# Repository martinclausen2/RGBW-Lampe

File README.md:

# RGBW-Lampe

The "RGBW-Lampe" projects allows to create full color lighting appliances.

## Features

- Four independent LED driver channels
  - Optimal to drive RGBW LED modules.
  - Mood light mode
  - High dynamic dimming range ideal for color mixing
- Status LED to indicate power on, channel, standby, and network status
- Brightness measurement to adjust brightness at power on
- IR remote control (receiver and sender)
  -	Option to network devices
- Single rotational encoder and switch needed to control
- Embedded terminal to control settings, clock, and alarms available via WLAN
  - Connect to home automation via MQTT
  - Adjust settings via exposed terminal
- Protected electronic power switch

## Technical Features
- ARM Cortex M3 based STM32L151A microcontroller
  - EEPROM for permanent storage of settings
- ESP8266 based WLAN connectivity ESP-12
- RC5 based communication (sender and receiver)
- Four PT4115 step-down LED driver
  - PWM input
  - LED driving current up to 1A
  - Short rise time of driving current to drive LED with very low duty PWM signals needed for color mixing
- Input voltage 9 to 15 V
- High dynamic brightness measurement with low cost phototransistor SFH320
- Pin header for observing and intercepting serial communication between MCU and WLAN module
  - Debugging
  - Initial programming of WLAN module
  - Redirecting communication to / from serial port of J-LINK
- PCB prepared (not used in current software) for 
  - Acceleration sensor
  - Pin headers for extension with additional I2C devices, LCD, or LED drivers
  - EEPROM from 24CXXX series with I2C connection - currently the MCU's internal EEPROM is utilized, the EEPROM can be populated if other STM32 MCU are to be used which do not contain a EEPROM

# Design description

## Hardware

### WLAN
The low cost WLAN module ESP-12 based on the ESP8266 is used to connect to home automation, expose an interface to configure the appliance, and to obtain date and time via NTP.

### MCU
The STM32L1 series features for this application relevant features like a large number of timers, and an embedded EEPROM.

The MCU can be programmed and debugged via SWD accessible through a custom pin header, that also exposes the serial port.

### LED Driver
Color mixing requires a large dimming range, which was realized via PWM dimming. The LED driver PT4115 has a short rise time allowing to create also very short current pulses to drive the LEDs at low levels.

### Logic Power Supply
A step down voltage regulator generates 3.3 V logic supply. It needs to be capable to provide good load regulation and sufficient current for the WLAN module as well as the IR-LED.

### RC5 receiver and sender

A IR emitting diode is driven by a small MOSFET from the PWM output of a timer in the MCU to send RC5 commands.

To receive RC5 commands the output of the IR receiver is sampled at a rate of about 4.5kHz by the MCU. The power supply of the IR receiver is cut in standby mode to prevent the battery to be drained prematurely.

### Brightness Sensor

The ambient brightness is sensed via an inexpensive and broadly available phototransistor SFA 320. To enhance the dynamic range, the MCU can switch the bias current between two different levels.
The precision is fully sufficient to adjust the brightness of the power LEDs at power on and dim the status LED in standby.

## Software

### WLAN Module

The time is fetched on start and about once per day later from the NTP server.

The terminal is exposed via port 22.

## Known Limitations
- The WLAN module may lose its connection when allowing Protected Management Frames (PMF) by the WLAN access point.
  - For Fritz!Box the option is found under WLAN -> Security -> Additional Security Settings
	 - German: Leave the option "Unterstützung für geschützte Anmeldungen von WLAN-Geräten (PMF) aktivieren" **unchecked**
- The WLAN module has fixed settings. Recompilation and flashing of the ESP8266 is needed to change them.
  - MQTT (device?.h)
  - WLAN (credentials.h)
  - NTP server (device?.h)
- The WLAN module exposes the ports of terminal (22) and MQTT without any protection.
- Commands received via MQTT and updates from the NTP server are injected into the terminal communication. Commands from the terminal might be interrupted by MQTT or time updates.
- OTA updates of the STM32 are not implemented yet.
- During power on, the LED driver operate at full current for a fraction of a second.

# User Manual

The user interface is rather simplistic.

Turning the encoder increases or decreases the brightness.
The integrated push button is used to select functionality and change between on and off.
Detailed settings can be adjusted via the serial terminal.

Coming from standby a short button press switches the light on. A long button press activates the networked mode, where other compatible lighting appliances receive commands to follow on, off, and brightness settings.

When the appliance in on the short button press selects between the four individual LED strings and a mode where the brightness is modulated between the channels.

When the button is pressed, the status led previews a for a short time the next selected functionality.

Standby can be reached via a long button pressed from power on mode.

| LED Color 	| Condition | Status   | 
| :------------ | :------ | :------- |
| red			|         | standby  |
| white			|         | power on |
| blue flashing | 1 flash, pause | WLAN module booting |
| blue flashing | 3 flash, pause | No time from NTP server obtained |
| green flash	| while adjusting brightness | maximum brightness reached |
| red flash		| while adjusting brightness | minimum brightness reached |
| white flash	| pressing the button short | selected white LED channel  |
| red flash		| pressing the button short | selected red LED channel |
| blue flash	| pressing the button short | selected blue LED channel |
| green flash	| pressing the button short | selected green LED channel |
| pink flash	| pressing the button short | selected mood light mode |
| green flash	| pressing the button very long | cancel button pressed |

The white flash is actually not visible, since the LED is already shining white.

# Configuration Manual

The serial port uses the following parameter 115200 Baud rate, data site 8, parity none, stop bits 1.

This terminal is exposed via the WLAN module to the user on port 22.

The commands can be listed by sending the command `help`.

## WLAN

WLAN credentials must be set at compile time in the file `credentials.h`.

## MQTT

Broker and node name must be defined at compile time in the file `device?.h`:

	#define MQTTbroker "192.168.178.123"
	#define nodename "RGBW-Lampe1"

Topics might be freely defined at compile time in the file `device?.h`. The following section contains some examples.

The appliance publishes to different topics its status:

	#define publishtopicstatus "RGBW-Lampe/1/status"
	#define publishtopicNTP "RGBW-Lampe/1/NTP"
	#define publishtopicswitch "RGBW-Lampe/1/switch"

The appliance subscribes to two topics defined at compile time in the file `device?.h`. The names are here choosen to be independent of the device id.

### MQTT to terminal forwarder

	#define subscribetopic "RGBW-Lampe"
All data is forwarded to the terminal of the MCU. See terminal section below for details.

### Switch

	#define subscribetopicswitch "RGBW-Lampe/switch"
The commands are `on` and `off`

## Commands Terminal

The terminal is accessible at three different routes:

- Interception of the serial WLAN - MCU communication through the pin header on the PCB
- Port 22 of the WLAN module
- MQTT topic defined by `subscribetopic`

### Set Brightness

	bright [type] <-c channel_no> <-b brightness_value>

set brightness values

| Type | Description |
| :--- | :--------- |
| 0 | Brightness last used before lights were switched off. |
| 1 | Minimum brightness when switched on |
| 2 | Maximum brightness any time |
| 3 | Maximum brightness when an alarm is triggered |
| 4 | PWM offset for brightness |
| 5 | Current brightness |

### Get External Brightness

	getextbright

Get the external brightness from the phototransistor

### Infrared Remote Control

	remote <-a address> <-rm receiver mode> <-sm sender mode> <-sa send address> <-sd send data>

set infrared remote parameters

| Mode | Decription |
| :--- | :--------- |
| 0 | Off |
| 1 | Alarm |
| 2 | Condional |
| 3 | All |

### Set Date and Time

	time [hour] [minute] [second]

set time of RTC

	date [2 digit year] [month] [day] [w] with w weekday

set date of RTC

	timestamp

get date and time from RTC

### Alarm

	alarmschedule [alarm no] <-w weekday> <-h hour> <-m minute>

set alarm schedule

	alarmsetting <-f time to fade-in light> <-si time to signal> <-sn snooze time>

set alarm parameters
	
	alarm <-a 1 | 0> <-s alarm skip count>

trigger, reset, set alarm skip count

### Beep

	beep <-s 1 | 0> volume - <-v volume> volume level - <-vl 1 | 0>

Call without any parameters to hear a beep. Using the `-s` parameter allows to turn the acoustic signal on and off. Volume allows for a continues selection of the volume between 0 and 255. The volume level sets the range in which the volume is adjustable.

### Power

	power <-l 1 | 0>

switch light.

### Reset Settings

	reset

reset settings to factory defaults

### Status LED

	statusled [flash count]

flash status led

### Mood light

	fadelight <-f 1 | 0> time - <-t time> <-b brightness> <-mb maximum brightness>

switch and parameterize on mood light

### DebugCmd

	debug

Dummy command to absorb debug messages from host.

### Reset WLAN Module

	resetesp

Reset network controller ESP8266.

### Version

	version

show STM32 software version

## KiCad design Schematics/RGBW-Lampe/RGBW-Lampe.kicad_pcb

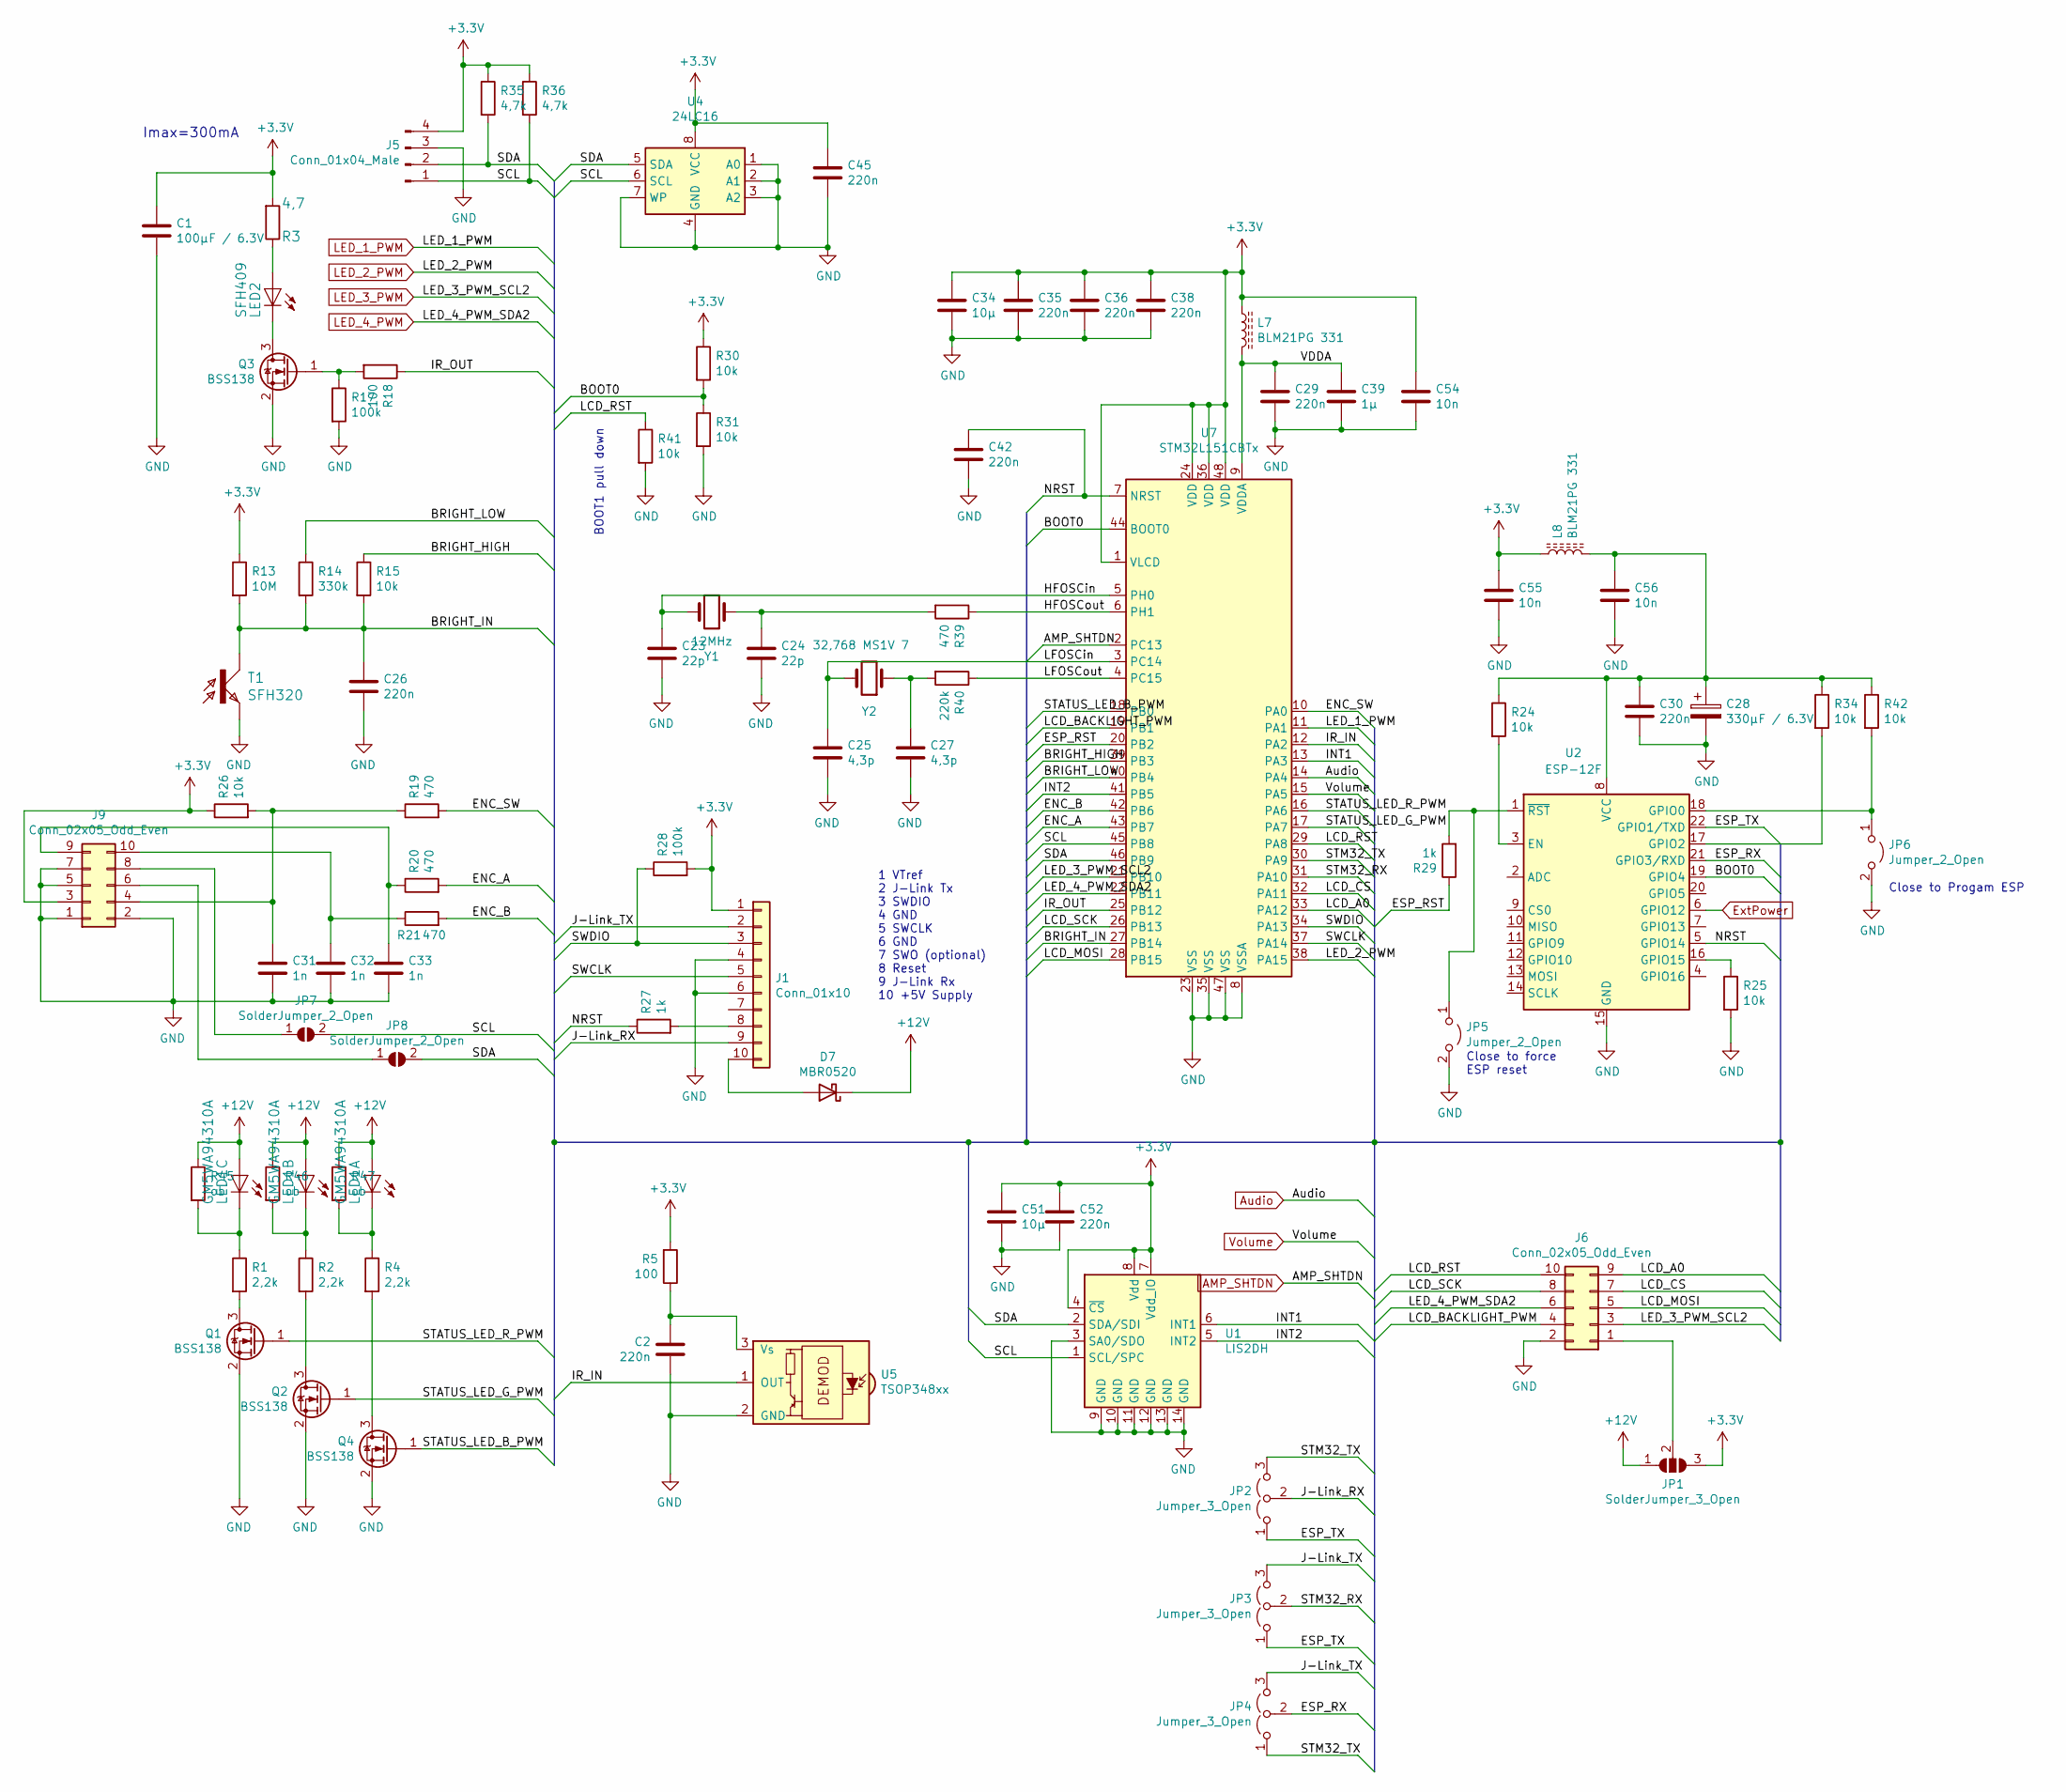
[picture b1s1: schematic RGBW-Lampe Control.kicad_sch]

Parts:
C1: 100µF / 6.3V; C_1210_3225Metric
C2, C26, C29, C30, C35, C36, C38, C42, C45, C52: 220n; C_0603_1608Metric
C23, C24: 22p; C_0603_1608Metric
C25, C27: 4,3p; C_0603_1608Metric
C28: 330µF / 6.3V; CP_Radial_D6.3mm_P2.50mm
C31, C32, C33: 1n; C_0603_1608Metric
C34, C51: 10µ; C_0805_2012Metric
C39: 1µ; C_0805_2012Metric
C54, C55, C56: 10n; C_0603_1608Metric
D7: MBR0520; D_SOD-123
J1: Conn_01x10; PinSocket_1x10_P1.27mm_Vertical
J5: Conn_01x04_Male; PinHeader_1x04_P2.54mm_Vertical
J6, J9: Conn_02x05_Odd_Even; IDC-Header_2x05_P2.54mm_Vertical
JP1: SolderJumper_3_Open; SolderJumper-3_P1.3mm_Open_RoundedPad1.0x1.5mm_NumberLabels
JP2, JP3, JP4: Jumper_3_Open; PinHeader_1x03_P2.54mm_Vertical
JP5, JP6: Jumper_2_Open; PinHeader_1x02_P2.54mm_Vertical
JP7, JP8: SolderJumper_2_Open; SolderJumper-2_P1.3mm_Open_Pad1.0x1.5mm
L7, L8: BLM21PG 331; L_0805_2012Metric
LED1: GM5WA94310A
LED2: SFH409; LED3MM
Q1, Q2, Q3, Q4: BSS138; SOT-23
R1, R2, R4: 2,2k; R_0805_2012Metric
R3: 4,7; R_1206_3216Metric
R5, R18: 100; R_0805_2012Metric
R13: 10M; R_0805_2012Metric
R14: 330k; R_0805_2012Metric
R15, R24, R25, R26, R30, R31, R34, R41, R42: 10k; R_0805_2012Metric
R17, R28: 100k; R_0805_2012Metric
R19, R20, R21, R39: 470; R_0805_2012Metric
R27, R29: 1k; R_0805_2012Metric
R35, R36: 4,7k; R_0805_2012Metric
R40: 220k; R_0805_2012Metric
R45, R46, R47: ob; R_0805_2012Metric
T1: SFH320; LED_PLCC-2
U1: LIS2DH; LGA-14_2x2mm_P0.35mm_LayoutBorder3x4y
U2: ESP-12F; ESP-12E
U4: 24LC16; SOIC-8_3.9x4.9mm_P1.27mm
U5: TSOP348xx; Vishay_MOLD-3Pin
U7: STM32L151CBTx; LQFP-48_7x7mm_P0.5mm
Y1: 12MHz; Crystal_SMD_EuroQuartz_MT-4Pin_3.2x2.5mm
Y2: 32,768 MS1V 7; Crystal_SMD_MicroCrystal_MS1V-T1K

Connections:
+3V3: C1.1, C34.1, C35.1, C36.1, C38.1, C45.1, C51.1, C52.1, C54.1, C55.1, J1.1, J5.4, J9.3, JP1.3 (B), L7.1, L8.1, R3.2, R5.2, R13.1, R26.1, R28.2, R30.1, R35.1, R36.1, U1.4 (~CS), U1.7 (Vdd_IO), U1.8 (Vdd), U4.8 (VCC), U7.1 (VLCD), U7.24 (VDD), U7.36 (VDD), U7.48 (VDD); also elsewhere on the board
+12V: D7.1 (K), JP1.1 (A), LED1.1 (A), LED1.2 (A), LED1.3 (A), R45.1, R46.1, R47.1; also elsewhere on the board
/Control/BOOT0: R30.2, R31.1, U2.19 (GPIO4), U7.44 (BOOT0)
/Control/BRIGHT_HIGH: R15.1, U7.39 (PB3)
/Control/BRIGHT_IN: C26.1, R13.2, R14.2, R15.2, T1.1 (C), U7.27 (PB14)
/Control/BRIGHT_LOW: R14.1, U7.40 (PB4)
/Control/ENC_A: R20.2, U7.43 (PB7)
/Control/ENC_B: R21.2, U7.42 (PB6)
/Control/ENC_SW: R19.2, U7.10 (PA0)
/Control/ESP_RST: R29.1, U7.20 (PB2)
/Control/ESP_RX: JP4.2 (C), U2.21 (GPIO3/RXD)
/Control/ESP_TX: JP2.1 (A), JP3.1 (A), U2.22 (GPIO1/TXD)
/Control/HFOSCin: C23.1, U7.5 (PH0), Y1.2
/Control/HFOSCout: R39.1, U7.6 (PH1)
/Control/INT1: U1.6 (INT1), U7.13 (PA3)
/Control/INT2: U1.5 (INT2), U7.41 (PB5)
/Control/IR_IN: U5.1 (OUT), U7.12 (PA2)
/Control/IR_OUT: R18.1, U7.25 (PB12)
/Control/J-Link_RX: J1.9, JP2.2 (C)
/Control/J-Link_TX: J1.2, JP3.3 (B), JP4.3 (B)
/Control/LCD_A0: J6.9, U7.33 (PA12)
/Control/LCD_BACKLIGHT_PWM: J6.4, U7.19 (PB1)
/Control/LCD_CS: J6.7, U7.32 (PA11)
/Control/LCD_MOSI: J6.5, U7.28 (PB15)
/Control/LCD_RST: J6.10, R41.1, U7.29 (PA8)
/Control/LCD_SCK: J6.8, U7.26 (PB13)
/Control/LFOSCin: C25.1, U7.3 (PC14), Y2.2
/Control/LFOSCout: R40.1, U7.4 (PC15)
/Control/NRST: C42.1, R27.1, U2.5 (GPIO14), U7.7 (NRST)
/Control/SCL: J5.1, JP7.2 (B), R36.2, U1.1 (SCL/SPC), U4.6 (SCL), U7.45 (PB8)
/Control/SDA: J5.2, JP8.2 (B), R35.2, U1.2 (SDA/SDI), U4.5 (SDA), U7.46 (PB9)
/Control/STATUS_LED_B_PWM: Q4.1 (G), U7.18 (PB0)
/Control/STATUS_LED_G_PWM: Q2.1 (G), U7.17 (PA7)
/Control/STATUS_LED_R_PWM: Q1.1 (G), U7.16 (PA6)
/Control/STM32_RX: JP3.2 (C), U7.31 (PA10)
/Control/STM32_TX: JP2.3 (B), JP4.1 (A), U7.30 (PA9)
/Control/SWCLK: J1.5, U7.37 (PA14)
/Control/SWDIO: J1.3, R28.1, U7.34 (PA13)
/Control/VDDA: C29.1, C39.1, L7.2, U7.9 (VDDA)
AMP_SHTDN: U7.2 (PC13); also elsewhere on the board
Audio: U7.14 (PA4); also elsewhere on the board
ExtPower: U2.6 (GPIO12); also elsewhere on the board
GND: C1.2, C2.2, C23.2, C24.2, C25.2, C26.2, C27.2, C28.2, C29.2, C30.2, C31.2, C32.2, C33.2, C34.2, C35.2, C36.2, C38.2, C39.2, C42.2, C45.2, C51.2, C52.2, C54.2, C55.2, C56.2, J1.4, J1.6, J5.3, J6.2, J9.1, J9.2, J9.5, J9.7, JP5.2 (B), JP6.2 (B), Q1.2 (S), Q2.2 (S), Q3.2 (S), Q4.2 (S), R17.2, R25.2, R31.2, R41.2, T1.2 (E), U1.3 (SA0/SDO), U1.9 (GND), U1.10 (GND), U1.11 (GND), U1.12 (GND), U1.13 (GND), U1.14 (GND), U2.15 (GND), U4.1 (A0), U4.2 (A1), U4.3 (A2), U4.4 (GND), U4.7 (WP), U5.2 (GND), U7.8 (VSSA), U7.23 (VSS), U7.35 (VSS), U7.47 (VSS); also elsewhere on the board
LED_1_PWM: U7.11 (PA1); also elsewhere on the board
LED_2_PWM: U7.38 (PA15); also elsewhere on the board
LED_3_PWM: J6.3, U7.21 (PB10); also elsewhere on the board
LED_4_PWM: J6.6, U7.22 (PB11); also elsewhere on the board
unnamed: C2.1, R5.1, U5.3 (Vs)
unnamed: C24.1, R39.2, Y1.1
unnamed: C27.1, R40.2, Y2.1
unnamed: C28.1, C30.1, C56.1, L8.2, R24.1, R34.1, R42.1, U2.8 (VCC)
unnamed: C31.1, J9.4, R19.1, R26.2
unnamed: C32.1, J9.10, R21.1
unnamed: C33.1, J9.9, R20.1
unnamed: D7.2 (A), J1.10
unnamed: J1.8, R27.2
unnamed: J6.1, JP1.2 (C)
unnamed: J9.6, JP8.1 (A)
unnamed: J9.8, JP7.1 (A)
unnamed: JP5.1 (A), R29.2, U2.1 (~RST)
unnamed: JP6.1 (A), R42.2, U2.18 (GPIO0)
unnamed: LED1.4 (C), R2.1, R46.2
unnamed: LED1.5 (C), R4.1, R47.2
unnamed: LED1.6 (C), R1.1, R45.2
unnamed: LED2.A, R3.1
unnamed: LED2.K (C), Q3.3 (D)
unnamed: Q1.3 (D), R1.2
unnamed: Q2.3 (D), R2.2
unnamed: Q3.1 (G), R17.1, R18.2
unnamed: Q4.3 (D), R4.2
unnamed: R24.2, U2.3 (EN)
unnamed: R25.1, U2.16 (GPIO15)
unnamed: R34.2, U2.17 (GPIO2)
Volume: U7.15 (PA5); also elsewhere on the board

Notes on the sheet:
BOOT1 pull down
1 VTref 2 J-Link Tx 3 SWDIO 4 GND 5 SWCLK 6 GND 7 SWO (optional) 8 Reset 9 J-Link Rx 10 +5V Supply
Close to Progam ESP
Imax=300mA
Close to force ESP reset

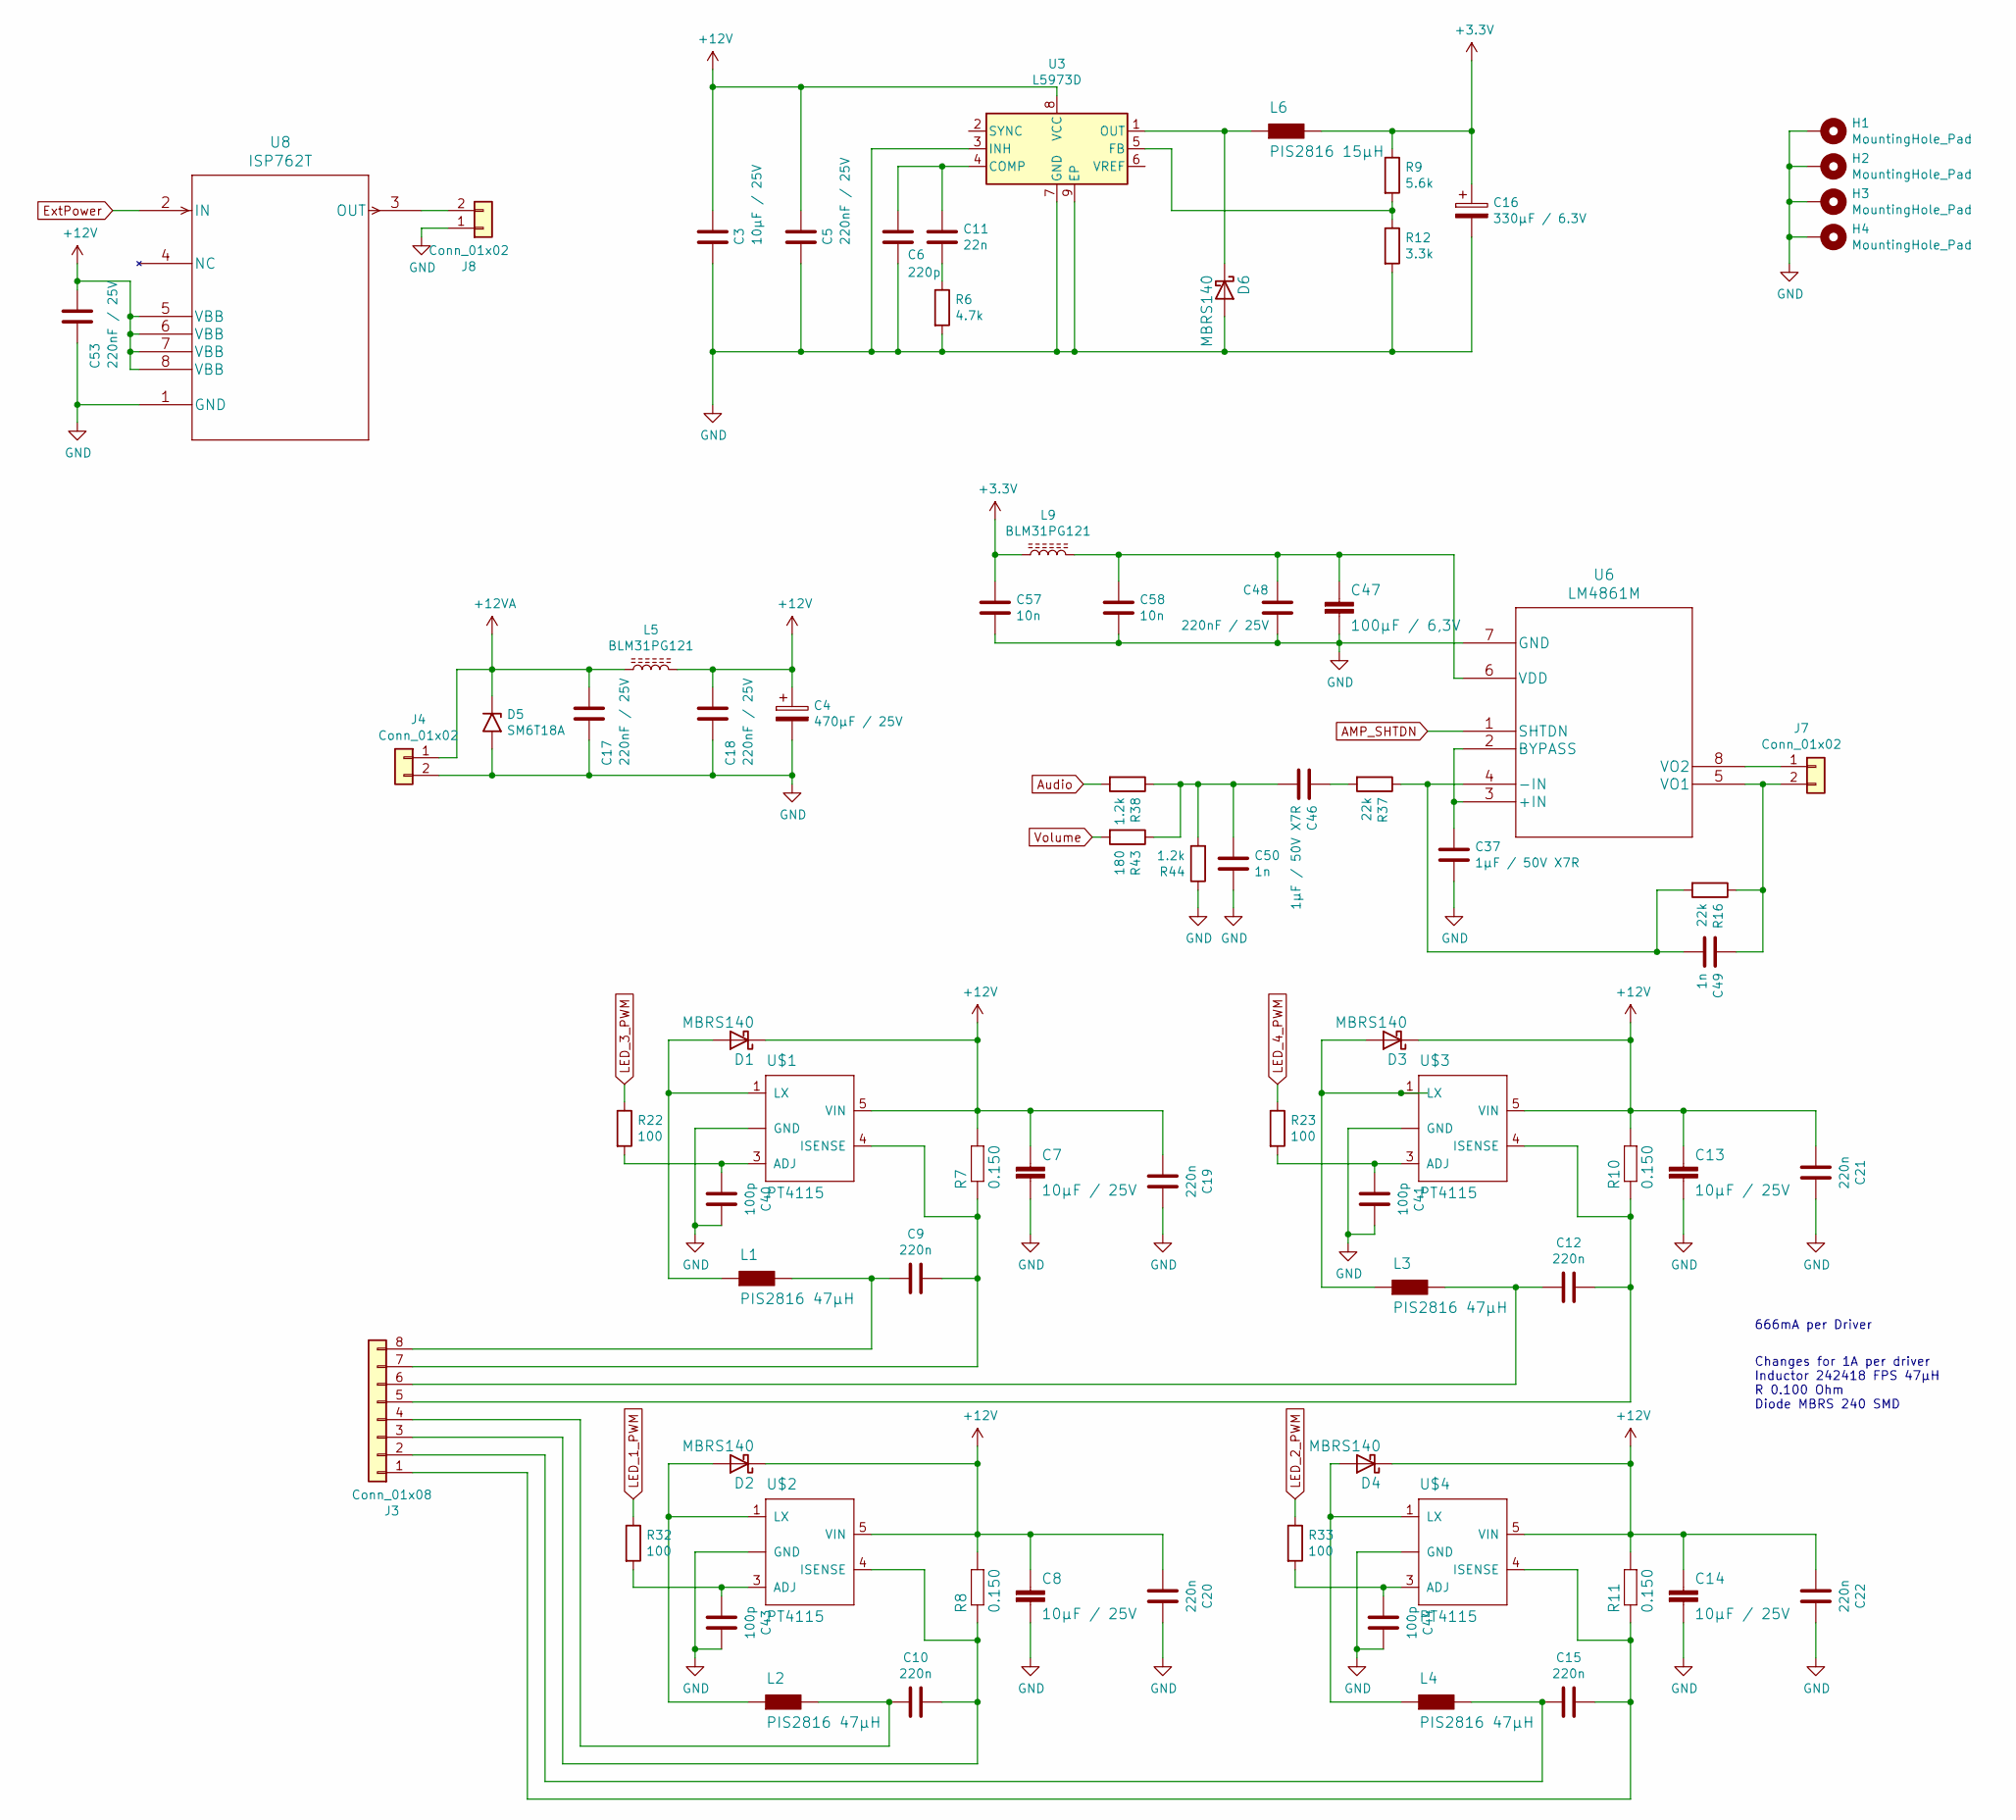
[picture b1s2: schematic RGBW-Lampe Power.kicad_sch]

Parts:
C3, C7, C8, C13, C14: 10µF / 25V; C_1206_3216Metric
C4: 470µF / 25V; CP_Radial_D8.0mm_P3.50mm
C5, C17, C18, C48, C53: 220nF / 25V; C_0603_1608Metric
C6: 220p; C_0603_1608Metric
C9, C10, C12, C15, C19, C20, C21, C22: 220n; C_0603_1608Metric
C11: 22n; C_0603_1608Metric
C16: 330µF / 6.3V; CP_Radial_D6.3mm_P2.50mm
C37, C46: 1µF / 50V X7R; C_1206_3216Metric
C40, C41, C43, C44: 100p; C_0603_1608Metric
C47: 100µF / 6,3V; C_1206_3216Metric
C49, C50: 1n; C_0603_1608Metric
C57, C58: 10n; C_0603_1608Metric
D1, D2, D3, D4, D6: MBRS140; D_SMB
D5: SM6T18A; D_SMB
H1, H2, H3, H4: MountingHole_Pad; MountingHole_3.2mm_M3_DIN965_Pad
J3: Conn_01x08; JST_XH_B8B-XH-A_1x08_P2.50mm_Vertical
J4, J7, J8: Conn_01x02; JST_XH_B2B-XH-A_1x02_P2.50mm_Vertical
L1, L2, L3, L4: PIS2816 47µH; PIS2816
L5, L9: BLM31PG121; L_1206_3216Metric
L6: PIS2816 15µH; PIS2816
R6: 4.7k; R_0805_2012Metric
R7, R8, R10, R11: 0.150; R_1210_3225Metric
R9: 5.6k; R_0805_2012Metric
R12: 3.3k; R_0805_2012Metric
R16, R37: 22k; R_0805_2012Metric
R22, R23, R32, R33: 100; R_0805_2012Metric
R38, R44: 1.2k; R_0805_2012Metric
R43: 180; R_0805_2012Metric
U3: L5973D; HSOP-8-1EP_3.9x4.9mm_P1.27mm_EP2.41x3.1mm_ThermalVias
U6: LM4861M
U8: ISP762T
U$1, U$2, U$3, U$4: PT4115; SOT89-5

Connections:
+3V3: C16.1, C57.2, L6.P$2, L9.1, R9.1; also elsewhere on the board
+12V: C3.1, C4.1, C5.2, C7.1, C8.1, C13.1, C14.1, C18.2, C19.2, C20.2, C21.2, C22.2, C53.2, D1.1 (K), D2.1 (K), D3.1 (K), D4.1 (K), L5.2, R7.2, R8.2, R10.2, R11.2, U3.8 (VCC), U8.5 (VBB), U8.6 (VBB), U8.7 (VBB), U8.8 (VBB), U$1.5 (VIN), U$2.5 (VIN), U$3.5 (VIN), U$4.5 (VIN); also elsewhere on the board
+12VA: C17.2, D5.1 (A1), J4.1, L5.1
AMP_SHTDN: U6.1 (SHTDN); also elsewhere on the board
Audio: R38.2; also elsewhere on the board
ExtPower: U8.2 (IN); also elsewhere on the board
GND: C3.2, C4.2, C5.1, C6.2, C7.2, C8.2, C13.2, C14.2, C16.2, C17.1, C18.1, C19.1, C20.1, C21.1, C22.1, C37.2, C40.1, C41.1, C43.1, C44.1, C47.2, C48.1, C50.1, C53.1, C57.1, C58.1, D5.2 (A2), D6.2 (A), H1.1, H2.1, H3.1, H4.1, J4.2, J8.1, R6.2, R12.2, R44.1, U3.3 (INH), U3.7 (GND), U3.9 (EP), U6.7 (GND), U8.1 (GND), U$1.2 (GND), U$1.2.1 (GND), U$2.2 (GND), U$2.2.1 (GND), U$3.2 (GND), U$3.2.1 (GND), U$4.2 (GND), U$4.2.1 (GND); also elsewhere on the board
LED_1_PWM: R32.1; also elsewhere on the board
LED_2_PWM: R33.1; also elsewhere on the board
LED_3_PWM: R22.1; also elsewhere on the board
LED_4_PWM: R23.1; also elsewhere on the board
unnamed: C9.1, J3.7, R7.1, U$1.4 (ISENSE)
unnamed: C9.2, J3.8, L1.P$2
unnamed: C10.1, J3.3, R8.1, U$2.4 (ISENSE)
unnamed: C10.2, J3.4, L2.P$2
unnamed: C6.1, C11.1, U3.4 (COMP)
unnamed: C11.2, R6.1
unnamed: C12.1, J3.5, R10.1, U$3.4 (ISENSE)
unnamed: C12.2, J3.6, L3.P$2
unnamed: C15.1, J3.1, R11.1, U$4.4 (ISENSE)
unnamed: C15.2, J3.2, L4.P$2
unnamed: C37.1, U6.2 (BYPASS), U6.3 (+IN)
unnamed: C40.2, R22.2, U$1.3 (ADJ)
unnamed: C41.2, R23.2, U$3.3 (ADJ)
unnamed: C43.2, R32.2, U$2.3 (ADJ)
unnamed: C44.2, R33.2, U$4.3 (ADJ)
unnamed: C46.1, R37.2
unnamed: C46.2, C50.2, R38.1, R43.1, R44.2
unnamed: C47.1, C48.2, C58.2, L9.2, U6.6 (VDD)
unnamed: C49.1, R16.2, R37.1, U6.4 (-IN)
unnamed: C49.2, J7.2, R16.1, U6.5 (VO1)
unnamed: D1.2 (A), L1.P$1, U$1.1 (LX)
unnamed: D2.2 (A), L2.P$1, U$2.1 (LX)
unnamed: D3.2 (A), L3.P$1, U$3.1 (LX)
unnamed: D4.2 (A), L4.P$1, U$4.1 (LX)
unnamed: D6.1 (K), L6.P$1, U3.1 (OUT)
unnamed: J7.1, U6.8 (VO2)
unnamed: J8.2, U8.3 (OUT)
unnamed: R9.2, R12.1, U3.5 (FB)
Volume: R43.2; also elsewhere on the board

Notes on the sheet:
Changes for 1A per driver Inductor 242418 FPS 47µH R 0.100 Ohm Diode MBRS 240 SMD
666mA per Driver

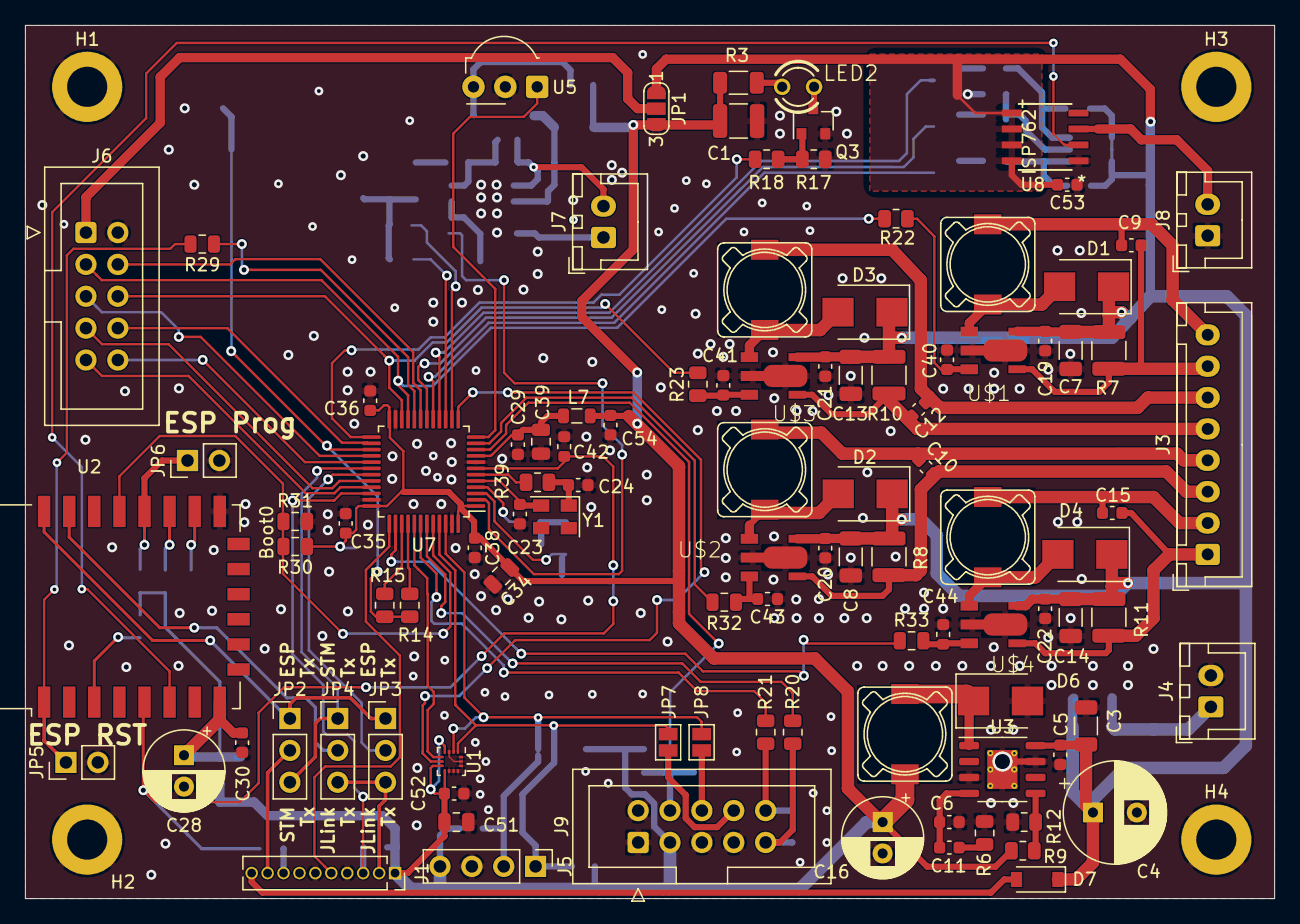
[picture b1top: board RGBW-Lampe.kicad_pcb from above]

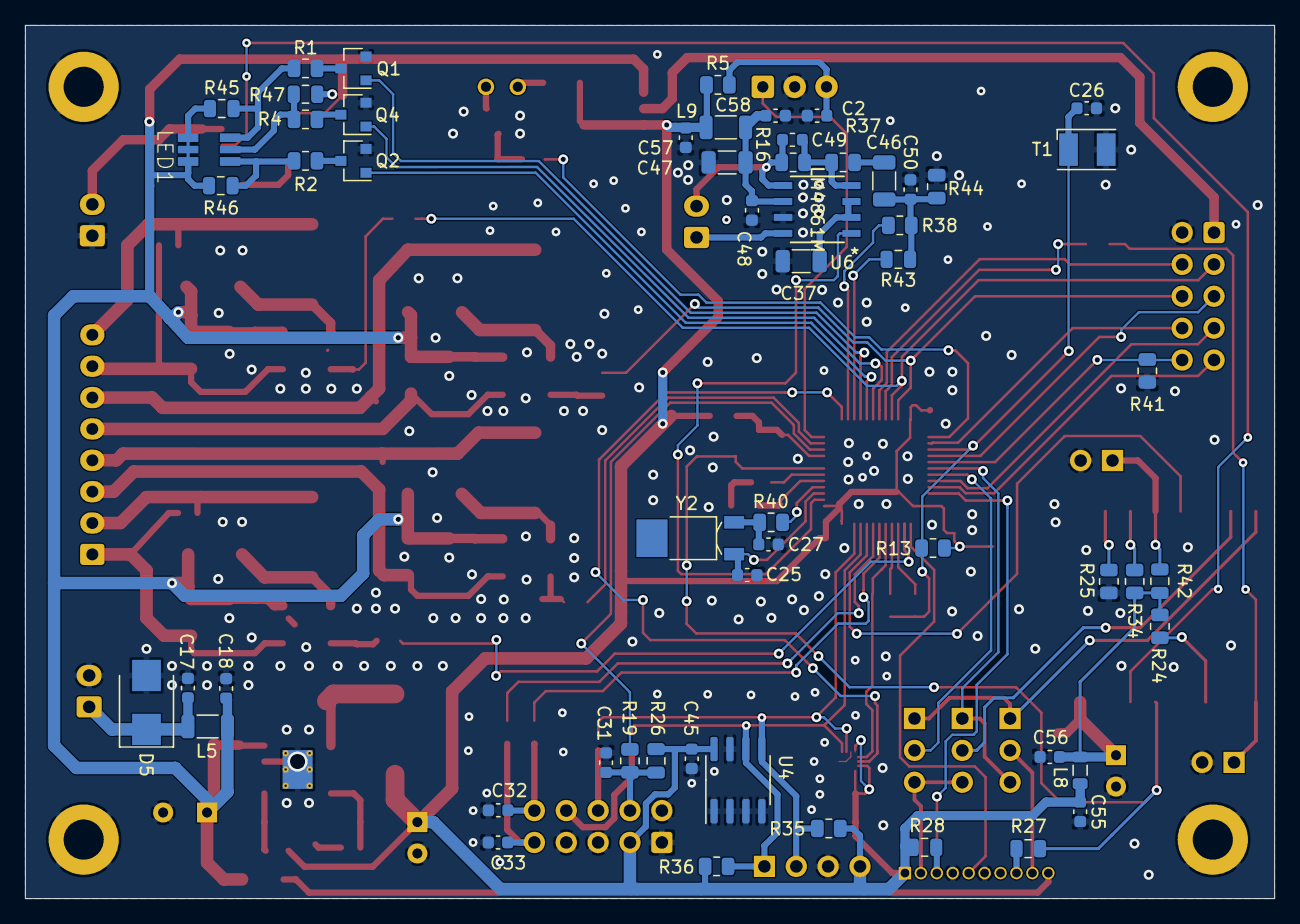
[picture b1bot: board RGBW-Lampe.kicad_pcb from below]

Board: 2 copper layers, 99.6 x 69.6 mm, 162 parts (57 on the bottom side), 103 nets.

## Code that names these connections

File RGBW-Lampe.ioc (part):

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Mcu.Name=STM32L151C(6-8-B)TxA
Mcu.Package=LQFP48
Mcu.UserName=STM32L151CBTxA
PA0-WKUP1.GPIOParameters=GPIO_PuPd,GPIO_Label
PA0-WKUP1.GPIO_Label=ENC_SW
PA0-WKUP1.GPIO_PuPd=GPIO_PULLUP
PA0-WKUP1.Signal=GPIO_Input
PA1.GPIOParameters=GPIO_Speed,GPIO_Label
PA1.GPIO_Label=LED_2_PWM
PA1.GPIO_Speed=GPIO_SPEED_FREQ_LOW
PA1.Signal=S_TIM2_CH2
PA10.GPIOParameters=GPIO_Speed,GPIO_PuPd
PA10.GPIO_PuPd=GPIO_PULLDOWN
PA10.GPIO_Speed=GPIO_SPEED_FREQ_HIGH
PA10.Mode=Asynchronous
PA10.Signal=USART1_RX
PA11.GPIOParameters=GPIO_Label
PA11.GPIO_Label=LCD_CS
PA11.Signal=GPIO_Output
PA12.GPIOParameters=GPIO_Label
PA12.GPIO_Label=LCD_A0
PA12.Signal=GPIO_Output
PA13.Mode=Serial_Wire
PA13.Signal=SYS_JTMS-SWDIO
PA14.Mode=Serial_Wire
PA14.Signal=SYS_JTCK-SWCLK
PA15.GPIOParameters=GPIO_Label
PA15.GPIO_Label=LED_1_PWM
PA15.Signal=S_TIM2_CH1_ETR
PA2.GPIOParameters=GPIO_Speed,GPIO_PuPd,GPIO_Label
PA2.GPIO_Label=IR_IN
PA2.GPIO_PuPd=GPIO_PULLUP
PA2.GPIO_Speed=GPIO_SPEED_FREQ_MEDIUM
PA2.Signal=S_TIM9_CH1
PA4.GPIOParameters=GPIO_Label
PA4.GPIO_Label=Audio
PA4.Signal=COMP_DAC1_group
PA5.GPIOParameters=GPIO_PuPd,GPIO_Label,GPIO_ModeDefaultOutputPP
PA5.GPIO_Label=Volume
PA5.GPIO_ModeDefaultOutputPP=GPIO_MODE_OUTPUT_OD
PA5.GPIO_PuPd=GPIO_NOPULL
PA5.Signal=GPIO_Output
PA6.GPIOParameters=GPIO_Label
PA6.GPIO_Label=STATUS_LED_R_PWM
PA6.Signal=S_TIM3_CH1
PA7.GPIOParameters=GPIO_Label
PA7.GPIO_Label=STATUS_LED_G_PWM
PA7.Signal=S_TIM3_CH2
PA8.GPIOParameters=GPIO_Label
PA8.GPIO_Label=LCD_RST
PA8.Signal=GPIO_Output
PA9.GPIOParameters=GPIO_Speed
PA9.GPIO_Speed=GPIO_SPEED_FREQ_HIGH
PA9.Mode=Asynchronous
PA9.Signal=USART1_TX
PB0.GPIOParameters=GPIO_Label
PB0.GPIO_Label=STATUS_LED_B_PWM
PB0.Signal=S_TIM3_CH3
PB1.GPIOParameters=GPIO_Label
PB1.GPIO_Label=LCD_BACKLIGHT_PWM
PB1.Signal=S_TIM3_CH4
PB10.GPIOParameters=GPIO_Label
PB10.GPIO_Label=LED_3_PWM_SCL2
PB10.Signal=S_TIM2_CH3
PB11.GPIOParameters=GPIO_Label
PB11.GPIO_Label=LED_4_PWM_SDA2
PB11.Signal=S_TIM2_CH4
PB12.GPIOParameters=GPIO_Speed,GPIO_PuPd,GPIO_Label
PB12.GPIO_Label=IR_OUT
PB12.GPIO_PuPd=GPIO_PULLDOWN
PB12.GPIO_Speed=GPIO_SPEED_FREQ_HIGH
PB12.Signal=S_TIM10_CH1
PB13.GPIOParameters=GPIO_Label
PB13.GPIO_Label=LCD_SCK
PB13.Mode=Simplex_Bidirectional_Master
PB13.Signal=SPI2_SCK
PB14.GPIOParameters=GPIO_Label
PB14.GPIO_Label=BRIGHT_IN
PB14.Mode=IN20
PB14.Signal=ADC_IN20
PB15.GPIOParameters=GPIO_Label
PB15.GPIO_Label=LCD_MOSI
PB15.Mode=Simplex_Bidirectional_Master
PB15.Signal=SPI2_MOSI
PB2.GPIOParameters=PinState,GPIO_Label
PB2.GPIO_Label=ESP_RST
PB2.PinState=GPIO_PIN_SET
PB2.Signal=GPIO_Output
PB3.GPIOParameters=PinState,GPIO_Label,GPIO_ModeDefaultOutputPP
PB3.GPIO_Label=BRIGHT_HIGH
PB3.GPIO_ModeDefaultOutputPP=GPIO_MODE_OUTPUT_PP
PB3.PinState=GPIO_PIN_SET
PB3.Signal=GPIO_Output
PB4.GPIOParameters=PinState,GPIO_Label
PB4.GPIO_Label=BRIGHT_LOW
PB4.PinState=GPIO_PIN_SET
PB4.Signal=GPIO_Output
PB6.GPIOParameters=GPIO_PuPd,GPIO_Label
PB6.GPIO_Label=ENC_B
PB6.GPIO_PuPd=GPIO_PULLUP
PB6.Signal=S_TIM4_CH1
PB7.GPIOParameters=GPIO_PuPd,GPIO_Label
PB7.GPIO_Label=ENC_A
PB7.GPIO_PuPd=GPIO_PULLUP
PB7.Signal=S_TIM4_CH2
PB8.GPIOParameters=GPIO_Pu
PB8.GPIO_Pu=GPIO_PULLUP
PB8.Mode=I2C
PB8.Signal=I2C1_SCL
PB9.GPIOParameters=GPIO_Pu
PB9.GPIO_Pu=GPIO_PULLUP
PB9.Mode=I2C
PB9.Signal=I2C1_SDA
PC13-WKUP2.GPIOParameters=PinState,GPIO_PuPd,GPIO_Label,GPIO_ModeDefaultOutputPP
PC13-WKUP2.GPIO_Label=AMP_SHTDN
PC13-WKUP2.GPIO_ModeDefaultOutputPP=GPIO_MODE_OUTPUT_PP
PC13-WKUP2.GPIO_PuPd=GPIO_NOPULL
PC13-WKUP2.PinState=GPIO_PIN_SET
PC13-WKUP2.Signal=GPIO_Output
PC14-OSC32_IN.Mode=LSE-External-Oscillator
PC14-OSC32_IN.Signal=RCC_OSC32_IN
PC15-OSC32_OUT.Mode=LSE-External-Oscillator
PC15-OSC32_OUT.Signal=RCC_OSC32_OUT
PH0-OSC_IN.Signal=RCC_OSC_IN
PH1-OSC_OUT.Signal=RCC_OSC_OUT
RCC.HSE_VALUE=24000000
RCC.SYSCLKFreq_VALUE=16000000
RCC.SYSCLKSource=RCC_SYSCLKSOURCE_HSI
board=custom

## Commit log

2021-03-28 Inital schematic and pin out
2021-06-05 first working version to control RGBW LED incl IR remote and debug output via serial port
2021-06-05 PCB version produced
2021-06-05 fix warnings fix cancel standby status led
2022-04-18 cleanup definitions to comply with more stringent gcc settings after update add struct to store settings.c started to add external brightness measurement added code skeleton for clock added frozen li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
2022-05-02 added dynamic pin configuration for external brightness measurement
2022-12-27 added missing linker script update lib version remove dead terminal integration
2022-12-27 added persistence for settings and last brightness measured via sensor code compiles is untested with respect to persistence and brightness measurement.
2022-12-28 added missing init for sender mode
2023-01-03 minor fixes
2023-01-09 added terminal as submodule
2023-04-05 include terminal as subproject migrate to newer ide version
    Does compile but not link!
2023-04-07 fix link error
2023-04-07 adding application specific terminal command file
2023-04-12 updated to new terminal code version
2023-04-12 get maxbrightness from settings added commands switched adc to registration of callback fixed main.c
2023-04-14 added alarm logic for light and sound
2023-04-14 added time and DAC config for sound generation
2023-04-15 fix and cleanup setbrightness.c set DAC DMA to circular
2023-04-16 added DAC HAl function calls
2023-05-07 fix potential div by zero fix UART DMA settings upgrade STM32cube version
2023-05-07 fixed external brightness measurement fixed terminal init fixed saving last brightness fixed commands adjusted settings
2023-05-09 included PWM offset in PWM wight calculation
2023-05-12 fix reception handler to process data outside of interrupt
2023-05-12 minor improvements on commands etc.
2023-05-13 added initial WLAN code added command to control status LED
2023-05-18 added code to generate acoustic alarm, sound quality not good yet
2023-05-19 fixed minor issues with acousticdddsalarm.c, bug stepcounter underflow still present
2023-05-20 fix beep
2023-05-20 fix acoustic alarm with new less computational intensive approach
2023-05-21 fix white space added files for mod light
2023-05-22 extended functionality to stretch time between consecutive dimming steps
2023-05-24 added initaial code fpr mood light - still buggy
2023-05-25 fix fade light
2023-05-30 added timeout to alarm fix warnings in fadelight.h and settigscommands.c
2023-05-31 added untested RC5 sender functionality TODO register callback for RC5 decoder
2023-05-31 switched from delay to pulse count via interrupt for RC5 Encoder bug no PWM signal from TIM10
2023-05-31 replace main callback with registered callbacks
2023-06-01 fix missing TIM10 output for RC5 encoder adjust RC5 pin and timing settings
2023-06-02 simplify RC5 encoder fix value in scaled sine table fix alarm sound start fix warnings added volume level control removed magic numbers
2023-06-02 fix alarm logic
2023-06-08 simplified array init set unused pins to analog
2023-06-10 minor code clean-up add missing array size
2023-07-16 added debug command to terminal added address entry to RC5 encoder command in terminal
2023-07-16 fix help
2023-07-16 cleanup logging
2023-09-19 first WLAN firmware with serial WLAN bridge, NTP client, and OTA interaction with STM32 firmware to be tested
2023-09-23 fix mutual reset signals between both MCU adjust presets ensure data from ESP8266 is received by STM32 by adding dealys after each data package
2023-09-24 added ESP reset fixed data loss in STM32 UART receiver code fixed light stayed on at power off when in light fading mode fix weekday numbering
2023-09-24 fix wrong date during day light saving at midnight.
2023-09-26 fix alarm skipcount decrease improve color changing pattern to avoid low light situation
2023-09-27 fix skip count
2023-09-28 fix alarm skip count
2023-10-07 fix missing time update when no client connected
2023-10-07 fix again alarmskipcount
2023-10-08 added error code output from ESp for STM32
2023-10-09 fix esp reset command add STM32 software version command removed delays after ESP send command via UART added command execute after every line termination
2023-10-09 remove unnecessary delay from sending via UART
2023-10-10 do not drive STM32 rst from ESP to avoid collision with STM32 debugger restart STM32 UART on error to handle ESP boot messages
2023-10-10 fix statusled function
2023-10-11 fix remote control from other lamp
2023-10-22 fix excessive end alarm command sent
2023-11-01 fix alarm end when command send via terminal add MQTT support to WLAN code
2023-11-04 added switch support and more status messages MQTT interface
2023-11-05 minor fix in terminal
2023-11-12 externalized device settings minor improvements on debug output update time via NTP only once a day
2023-11-27 migrate to newer CubeMX version
2023-12-16 updated kicad version
2023-12-23 added README.md
2023-12-23 minor fixes to README.md
2023-12-24 extended README.md
2023-12-25 fix encoder
2024-01-07 fix alarm start and end send via RC5
2024-01-09 remove dead code and fix brightness settings
2024-01-24 fix fadelight
2024-04-28 update CUBE MX version fix RC5 sender: duty cycle and toggle bit
